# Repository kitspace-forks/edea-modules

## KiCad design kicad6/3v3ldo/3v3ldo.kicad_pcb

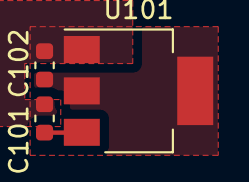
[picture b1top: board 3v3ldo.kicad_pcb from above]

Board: 2 copper layers, 3 parts (0 on the bottom side), 3 nets.

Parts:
C101, C102: 1uF; C_0603_1608Metric
U101: NCP1117-3.3_SOT223; SOT-223-3_TabPin2

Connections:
/GND: C101.2, C102.2, U101.1
/VIN: C101.1, U101.3
/VOUT: C102.1, U101.2

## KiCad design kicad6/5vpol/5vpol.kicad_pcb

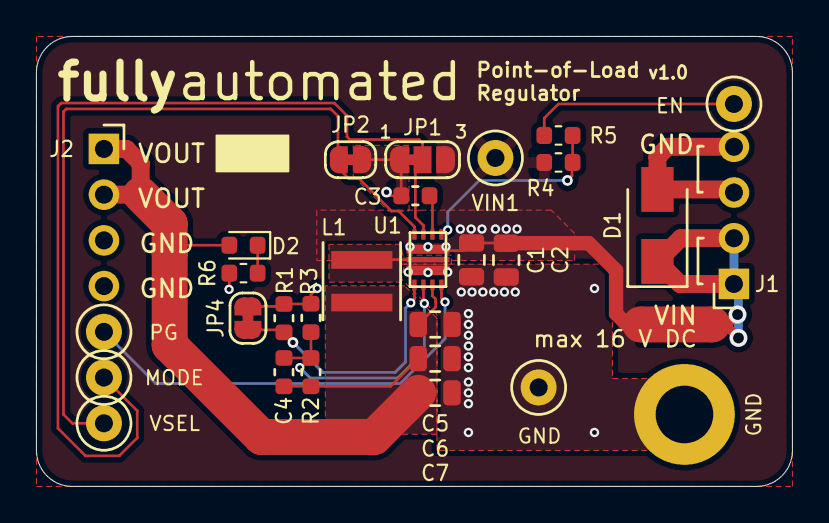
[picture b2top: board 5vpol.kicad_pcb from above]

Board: 2 copper layers, 42.0 x 25.0 mm, 31 parts (1 on the bottom side), 14 nets.

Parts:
C1, C2: 2.2uF/25V; C_0805_2012Metric
C3: 100nF/25V; C_0603_1608Metric
C4: 22pF/50V; C_0603_1608Metric
C5, C6, C7: 10uF/6.3V; C_0805_2012Metric
D1: SMAJ15A-13-F; D_SMA
D2: LED_Small_ALT; LED_0603_1608Metric
EN: EN; TestPoint_Loop_D1.80mm_Drill1.0mm_Beaded
G1: Fully_Automated_Logo; fully_automated_logo_soldermask
H1: MountingHole_Pad; MountingHole_3.2mm_M3_DIN965_Pad
J1: IN; PinSocket_1x04_P2.54mm_Horizontal
J2: OUT; PinSocket_1x04_P2.54mm_Horizontal
JP1: SolderJumper_3_Bridged12; SolderJumper-3_P1.3mm_Bridged12_RoundedPad1.0x1.5mm_NumberL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
JP2, JP4: SolderJumper_2_Bridged; SolderJumper-2_P1.3mm_Bridged_RoundedPad1.0x1.5mm
L1: XGL4020-102ME_; L_Coilcraft_XxL4020
MODE1: MODE; TestPoint_Loop_D1.80mm_Drill1.0mm_Beaded
NT1: Net-Tie_2; NetTie-2_SMD_Pad2.0mm
PG1: PG; TestPoint_Loop_D1.80mm_Drill1.0mm_Beaded
R1: dnp; R_0603_1608Metric
R2: 240k; R_0603_1608Metric
R3: 39k; R_0603_1608Metric
R4: 10k; R_0603_1608Metric
R5: 100; R_0603_1608Metric
R6: 2k2; R_0603_1608Metric
TP1: GND; TestPoint_Loop_D1.80mm_Drill1.0mm_Beaded
U1: TPS62135; RGX_TI_VQFN-HR11
VIN1: VIN; TestPoint_Loop_D1.80mm_Drill1.0mm_Beaded
VSEL1: VSEL; TestPoint_Loop_D1.80mm_Drill1.0mm_Beaded

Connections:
+5V: C4.1, C5.1, C6.1, C7.1, D2.2, J2.1, J2.2, L1.2, R2.1, U1.6
/TPS62135 Power Supply/FB: C4.2, R2.2, R3.1, U1.5
/TPS62135 Power Supply/MODE: JP1.2, MODE1.1, U1.10
/TPS62135 Power Supply/PGOOD: PG1.1, U1.7
/TPS62135 Power Supply/SW: L1.1, U1.2
GND: C1.2, C2.2, C3.2, C5.2, C6.2, C7.2, D1.2, H1.1, J1.3, J1.4, J2.3, J2.4, JP1.1, JP2.1, JP4.2, R1.2, R3.2, R6.2, TP1.1, U1.3
unnamed: C1.1, C2.1, JP1.3, NT1.2, R4.2, U1.1, VIN1.1
unnamed: C3.1, U1.9
unnamed: D2.1, R6.1
unnamed: EN.1, R5.1
unnamed: JP2.2, U1.11, VSEL1.1
unnamed: JP4.1, R1.1, U1.4
unnamed: R4.1, R5.2, U1.8
VBUS: D1.1, J1.1, J1.2, NT1.1

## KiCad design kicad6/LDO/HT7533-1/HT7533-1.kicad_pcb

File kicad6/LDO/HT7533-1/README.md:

# HT7533-1

This is 100mA LDO with fixed 3.3V output and up to 30V Vin.

## JLC Compatible

All parts are JLC basic parts.

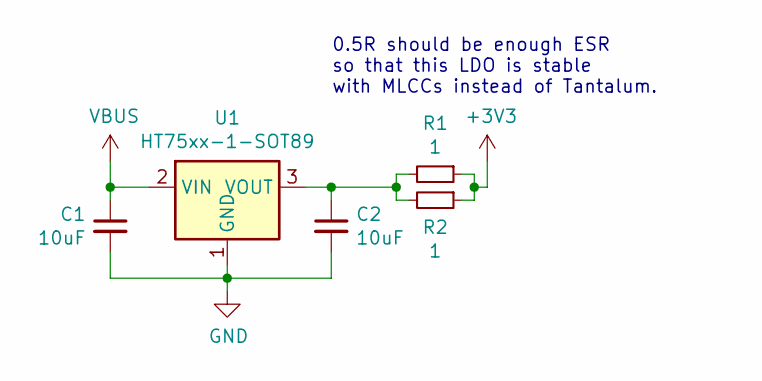
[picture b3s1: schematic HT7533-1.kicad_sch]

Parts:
C1, C2: 10uF; C_0603_1608Metric; MPN CL10A106KP8NNNC; JLC 0603
R1, R2: 1; R_0402_1005Metric; JLC 0402
U1: HT75xx-1-SOT89; SOT-89-3; JLC SOT-89-3

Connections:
+3V3: R1.1, R2.1
GND: C1.2, C2.2, U1.1 (GND)
unnamed: C2.1, R1.2, R2.2, U1.3 (VOUT)
VBUS: C1.1, U1.2 (VIN)

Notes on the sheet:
0.5R should be enough ESR so that this LDO is stable with MLCCs instead of Tantalum.

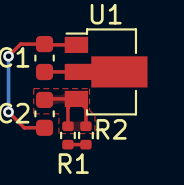
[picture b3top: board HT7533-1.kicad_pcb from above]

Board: 2 copper layers, 5 parts (0 on the bottom side), 4 nets.

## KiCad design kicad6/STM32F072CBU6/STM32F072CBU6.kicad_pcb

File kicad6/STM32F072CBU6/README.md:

# STM32F072CBU6

This module provides the STM32F072 in a 48-Pin VQFN package.

## Datasheets

- [STM32F072CB](https://www.st.com/resource/en/datasheet/stm32f072cb.pdf)
- [Reference Manual](https://www.st.com/resource/en/reference_manual/dm00031936-stm32f0x1stm32f0x2stm32f0x8-advanced-armbased-32bit-mcus-stmicroelectronics.pdf)

## Routing

No special assumptions, except for the existance of a Ground-plane, were made. The 3V3 rail was routed
without a 3V3 plane in mind in case this gets used in a more constrained setup.

## Debug Connector

The footprint for a TC2030 connector is present for debugging-purposes.

## JLC Compatible

All parts, except the STM32F072 are basic parts and have been choosen to be compatible
with the Microcontroller.

## Tolerances, Traces & Vias

Trace widths, Vias and spacing are compatible with 2oz outer layer on with common tolerances.
If lower tolerances are available, the traces and caps can be moved around still to make it
a bit more compact.

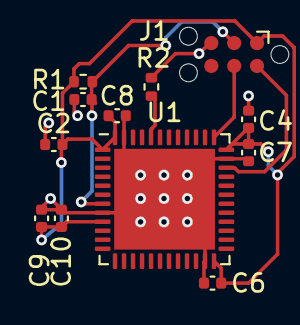
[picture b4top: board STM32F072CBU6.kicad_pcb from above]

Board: 2 copper layers, 12 parts (0 on the bottom side), 6 nets.

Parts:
C1, C2, C6, C7, C8: 100nF; C_0402_1005Metric
C4: 4.7uF; C_0402_1005Metric
C9: 1uF; C_0402_1005Metric
C10: 10nF; C_0402_1005Metric
J1: DBG; Tag-Connect_TC2030-IDC-NL_2x03_P1.27mm_Vertical
R1, R2: 10k; R_0402_1005Metric
U1: STM32F072CBUx; QFN-48-1EP_7x7mm_P0.5mm_EP5.6x5.6mm

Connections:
+3V3: C2.2, C4.2, C6.2, C7.2, C8.2, C9.2, C10.2, J1.1, R1.1, U1.1, U1.9, U1.24, U1.36, U1.48
/NRST: C1.2, J1.3, R1.2, U1.7
/SWCLK: J1.4, U1.37
/SWDIO: J1.2, U1.34
GND: C1.1, C2.1, C4.1, C6.1, C7.1, C8.1, C9.1, C10.1, J1.5, R2.2, U1.8, U1.23, U1.35, U1.47, U1.49
unnamed: R2.1, U1.44

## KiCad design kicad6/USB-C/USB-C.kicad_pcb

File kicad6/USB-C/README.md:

# USB-C Connector

This module provides a simple, USB-C receptacle including necessary protections and passives.
It is configured as a Sink/Device.

The 1.5k resistor should not be populated, except if the downstream (e.g. MCU) does not have a built-in one.

## JLC Compatible

Both the connector and the ESD-protection diode are extended parts, the rest of the passives
are basic parts.

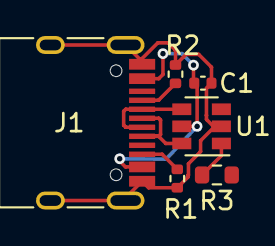
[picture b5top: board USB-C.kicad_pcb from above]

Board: 2 copper layers, 6 parts (0 on the bottom side), 7 nets.

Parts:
C1: 100nF; C_0402_1005Metric
J1: USB_C_Receptacle_USB2.0; USB_C_Receptacle_HRO_TYPE-C-31-M-12
R1, R2: 5.1k; R_0402_1005Metric
R3: 1.5k; R_0603_1608Metric
U1: USBLC6-2SC6; SOT-23-6

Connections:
/D+: R3.2, U1.1
/USB_D+: J1.A6, J1.B6, U1.6
/USB_D-: J1.A7, J1.B7, U1.4
GND: C1.2, J1.A1, J1.A12, J1.B1, J1.B12, J1.S1, R1.2, R2.2, U1.2
unnamed: J1.A5, R2.1
unnamed: J1.B5, R1.1
VBUS: C1.1, J1.A4, J1.A9, J1.B4, J1.B9, U1.5
